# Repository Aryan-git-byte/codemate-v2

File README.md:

# Overview:

# What is this??
Yo, this is a 4x4 custom macropad that you can use for making ur life ezz, lol
it has 16 macros, 2 rotary encoders, RGB lights and an OLED display. and also it is a successor of my previous macropad [Codemate](https://github.com/aryan-git-byte/codemate).
# Use case:
whether you are a programmer, 3d modeller, editor or whatever u can easily use this macropad with just a little bit tweak in its firmware.
# Schematic Overview:
this is the schematic of the project, which u can see here:

you can see the MCU, the key matrix, the LEDs, encoders, everything in this schematic.
# why i made it??
cuz i believe that having a macropad can ezz my workflow and also give make it faster and more efficient.
# PCB overview:
for this i am using a 2 layer pcb board:

# How to Assemble
1. get the pcb ordered and solder all the components to it carefully
2. get these things 3d printed:
    1. [top-plate](3D-models/printable/TopPanel.stl) - 1x
    2. [main-body](3D-models/printable/Main-Body.stl) - 1x
    3. [keycaps](<3D-models/printable/DSA 1u.step>) - 16x
    4. [encoders](3D-models/printable/EncoderKnob.step) - 2x
3. cover it with the top plate
4. drill a 2 mm hole near the red holes:

5. insert 4 m3 inserts in these holes on the main body.
6. Now, put the soldered pcb with all the components inside the main-body
7. put the top panel , and put m3 screws. 
8. now put the keycaps and the knob onto it.
9. enjoy <3
# Firmware:
written in Arduino framework for ESP32-S3 Zero using these libraries:
- [FastLED](https://github.com/FastLED/FastLED) — RGB control
- [Keypad](https://github.com/Chris--A/Keypad) — key matrix
- [Adafruit SSD1306](https://github.com/adafruit/Adafruit_SSD1306) — OLED
- [Adafruit PCF8574](https://github.com/adafruit/Adafruit-PCF8574) — IO expander for encoders
- USB HID (built into ESP32 Arduino core) — keyboard + media keys

### flashing steps:
1. opem [Arduino IDE](https://www.arduino-cc/en/software)
2. add ESP32 board support — paste this in Board Manager URL:
   `https://raw.githubusercontent.com/espressif/arduino-esp32/gh-pages/package_esp32_index.json`
3. install the libraries above from Library Manager
4. select board: `ESP32S3 Dev Module`
5. plug in USB into the devboard
6. upload `firmware/firmware.ino` from this repo
7. done
# BOM:
|item name | quantity | unit price | link | total price
|-|-|-|-|-
Esp32-s3 zero development board|1| 620 rs | [link](https://hubtronics.in/esp32-s3-zero-m?srsltid=AfmBOoq3kT32v8UczG0TNtBfSk1mz6VMTDCRHNpQfM2GaU1SiqyRmEIawpQ)| 620 rs 
Blue MX cherry switches ( pack of 10)| 2 | 350 rs | [link](https://meckeys.com/shop/accessories/keyboard-accessories/key-switches/cherry-mx2a-switch/)| 700 rs
Oled 0.91"|1|198 rs |[link](https://hubtronics.in/0.91inch-4pin-oled-display-module?srsltid=AfmBOookZKpAjyAl9gw9jcReCTK7EAOUjZujy9mtLwreZrFGmea6Y7Tw4Bo)|198 rs 
PCF8574AP | 1 | 124 rs | [link](https://robu.in/product/pcf8574an-texas-instruments-pcf8574an-i-o-expander-8-bit-i2c-2-5-v-6-v-dip-16-pins/)|128 rs
EC11 rotary encoder|2|64 rs | [link](https://www.flyrobo.in/15mm-ec11-rotary-encoder-with-switch-digital-potentiometer?tracking=ads&srsltid=AfmBOoolmlw6qAxzYU2i8ZVPycIOWE9vltP8OnFKiRVbvLtu4q_V_7MlLQc) | 128 rs 
WS2812B | 40 | 4.72 rs | [link](https://hubtronics.in/ws2812b-5050-led?srsltid=AfmBOopNwODVwO3OMV0OqoXZXVZTHtyzRN5Mug-3Q1g00d0sAzbv55LT4r4)| 188.80 rs
470 ohm 0805 resistor (pack of 20)| 1| 8 rs | [link](https://quartzcomponents.com/products/470ohm-470e-5-smd-resistor-0805-pack-of-20-pieces?variant=43515854749930&country=IN&currency=INR&utm_medium=product_sync&utm_source=google&utm_content=sag_organic&utm_campaign=sag_organic&srsltid=AfmBOop0LmdszysC6QKr0nqkLmwG5YoMJAUPzzIZ7T8eKz9CffIsIlRdmUY)|8 rs
100 nF Capacitor 0603 (pack of 20)|2|11 rs | [link](https://quartzcomponents.com/products/kemet-100nf-50v-0603-smd-pack-x7r-multilayer-ceramic-capacitor-10-tolerence-pack-of-20?variant=45972486193386&country=IN&currency=INR&utm_medium=product_sync&utm_source=google&utm_content=sag_organic&utm_campaign=sag_organic&srsltid=AfmBOopnfKv3gKdibyX3qxzEoiDa6hgtUaGOK5H7Lh-MDVl_BFFMZAF-OTY)| 22 rs
 Diode (1N4148)|25|3 rs |[link](https://quartzcomponents.com/products/1n4148-zener-diode?variant=42817413546218&country=IN&currency=INR&utm_medium=product_sync&utm_source=google&utm_content=sag_organic&utm_campaign=sag_organic&srsltid=AfmBOooP8why-3JDRTveRI7fR_9TvlunJk5nlbo3Xbwx15PTjlmVHmHTaeQ)|75 rs
hubtroncs shipping charge| 1 | 75 rs | | 75 rs 
Meckkeys shipping charge | 1 | 100 rs | | 100 rs
FlyRobo shipping | 1 | 59 rs | | 59 rs 

[ Note: the components from the quartz component and robu are budled with my other order of different project, otherwise if u are ordering it for yourself , it will be 100 rs each ]

Total: 2301 rs , (24 usd)

## PCB will be :   

7 usd, shipping will be another 10 usd, but i m getting this shipped along with my different pcb.

# grand total : 31 usd

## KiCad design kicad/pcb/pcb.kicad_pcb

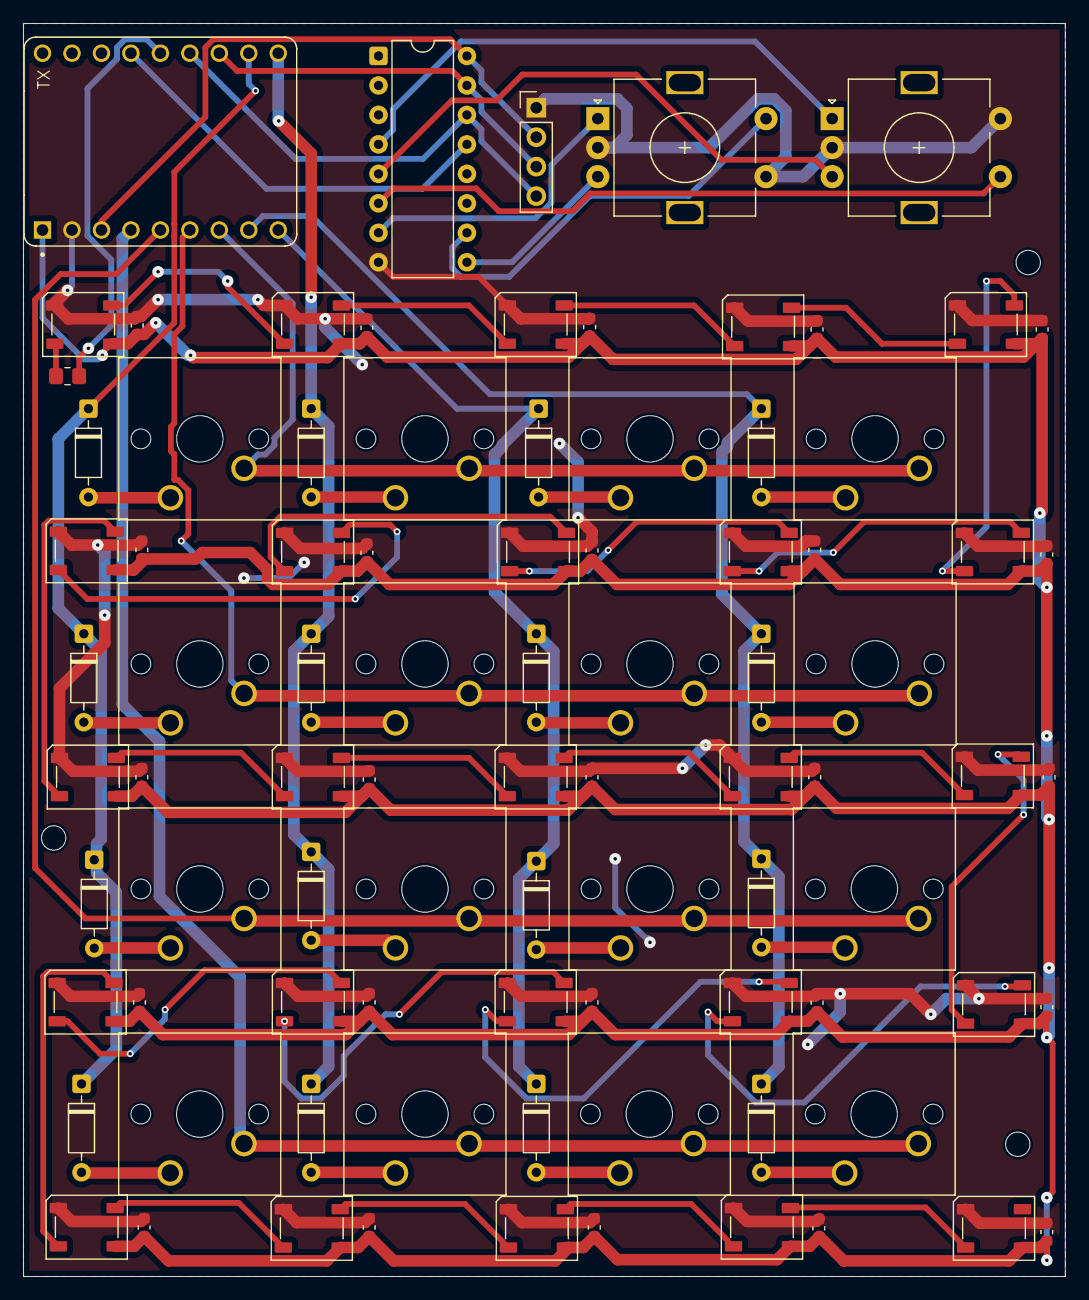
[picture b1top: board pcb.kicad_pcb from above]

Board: 2 copper layers, 89.8 x 108.0 mm, 88 parts (0 on the bottom side), 62 nets.

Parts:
C1, C2, C3, C4, C5, C6, C7, C8, C9, C10, C11, C12, C13, C14, C15, C16, C17, C18, C19, C20, C21, C22, C23, C24, C25: 100 nF; C_0603_1608Metric
D1, D2, D3, D4, D5, D6, D7, D8, D9, D10, D11, D12, D13, D14, D15, D16: D; D_DO-35_SOD27_P7.62mm_Horizontal
D17, D18, D19, D20, D21, D22, D23, D24, D25, D26, D27, D28, D29, D30, D31, D32, D33, D34, D35, D36, D37, D38, D39, D40, D41: WS2812B; LED_WS2812B_PLCC4_5.0x5.0mm_P3.2mm
J1: Conn_01x04; PinHeader_1x04_P2.54mm_Vertical
R1: 470; R_0805_2012Metric_Pad1.20x1.40mm_HandSolder
SW1, SW2, SW3, SW4, SW5, SW6, SW7, SW8, SW9, SW10, SW11, SW12, SW13, SW14, SW15, SW16: SW_SPST; SW_Cherry_MX_1.00u_PCB
SW17, SW18: RotaryEncoder_Switch; RotaryEncoder_Alps_EC11E-Switch_Vertical_H20mm
U1: ESP32-S3-ZERO; MODULE_ESP32-S3-ZERO
U2: PCF8574AP; DIP-16_W7.62mm

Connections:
+3V3: J1.2, U1.3V3 (3V3(OUT)), U2.16 (VDD)
+5V: C1.2, C2.2, C3.2, C4.2, C5.2, C6.2, C7.2, C8.2, C9.2, C10.2, C11.2, C12.2, C13.2, C14.2, C15.2, C16.2, C17.2, C18.2, C19.2, C20.2, C21.2, C22.2, C23.2, C24.2, C25.2, D17.1 (VDD), D18.1 (VDD), D19.1 (VDD), D20.1 (VDD), D21.1 (VDD), D22.1 (VDD), D23.1 (VDD), D24.1 (VDD), D25.1 (VDD), D26.1 (VDD), D27.1 (VDD), D28.1 (VDD), D29.1 (VDD), D30.1 (VDD), D31.1 (VDD), D32.1 (VDD), D33.1 (VDD), D34.1 (VDD), D35.1 (VDD), D36.1 (VDD), D37.1 (VDD), D38.1 (VDD), D39.1 (VDD), D40.1 (VDD), D41.1 (VDD), U1.5V
/INT: U1.12 (GP12), U2.13 (~INT)
/SCL: J1.4, U1.10 (GP10), U2.14 (SCL)
/SDA: J1.3, U1.9 (GP9), U2.15 (SDA)
C1: SW1.2 (B), SW5.2 (B), SW9.2 (B), SW13.2 (B), U1.1 (GP1)
C2: SW2.2 (B), SW6.2 (B), SW10.2 (B), SW14.2 (B), U1.2 (GP2)
C3: SW3.2 (B), SW7.2 (B), SW11.2 (B), SW15.2 (B), U1.3 (GP3)
C4: SW4.2 (B), SW8.2 (B), SW12.2 (B), SW16.2 (B), U1.4 (GP4)
GND: C1.1, C2.1, C3.1, C4.1, C5.1, C6.1, C7.1, C8.1, C9.1, C10.1, C11.1, C12.1, C13.1, C14.1, C15.1, C16.1, C17.1, C18.1, C19.1, C20.1, C21.1, C22.1, C23.1, C24.1, C25.1, D17.3 (VSS), D18.3 (VSS), D19.3 (VSS), D20.3 (VSS), D21.3 (VSS), D22.3 (VSS), D23.3 (VSS), D24.3 (VSS), D25.3 (VSS), D26.3 (VSS), D27.3 (VSS), D28.3 (VSS), D29.3 (VSS), D30.3 (VSS), D31.3 (VSS), D32.3 (VSS), D33.3 (VSS), D34.3 (VSS), D35.3 (VSS), D36.3 (VSS), D37.3 (VSS), D38.3 (VSS), D39.3 (VSS), D40.3 (VSS), D41.3 (VSS), J1.1, SW17.C, SW17.S1, SW18.C, SW18.S2, U1.GND, U2.8 (GND)
unnamed: D1.2 (A), SW1.1 (A)
unnamed: D2.2 (A), SW2.1 (A)
unnamed: D3.2 (A), SW3.1 (A)
unnamed: D4.2 (A), SW4.1 (A)
unnamed: D5.2 (A), SW5.1 (A)
unnamed: D6.2 (A), SW6.1 (A)
unnamed: D7.2 (A), SW7.1 (A)
unnamed: D8.2 (A), SW8.1 (A)
unnamed: D9.2 (A), SW9.1 (A)
unnamed: D10.2 (A), SW10.1 (A)
unnamed: D11.2 (A), SW11.1 (A)
unnamed: D12.2 (A), SW12.1 (A)
unnamed: D13.2 (A), SW13.1 (A)
unnamed: D14.2 (A), SW14.1 (A)
unnamed: D15.2 (A), SW15.1 (A)
unnamed: D16.2 (A), SW16.1 (A)
unnamed: D17.4 (DIN), D18.2 (DOUT)
unnamed: D17.2 (DOUT), D29.4 (DIN)
unnamed: D18.4 (DIN), D19.2 (DOUT)
unnamed: D19.4 (DIN), D28.2 (DOUT)
unnamed: D20.4 (DIN), D21.2 (DOUT)
unnamed: D20.2 (DOUT), D27.4 (DIN)
unnamed: D21.4 (DIN), D22.2 (DOUT)
unnamed: D22.4 (DIN), D30.2 (DOUT)
unnamed: D23.4 (DIN), D24.2 (DOUT)
unnamed: D23.2 (DOUT), D31.4 (DIN)
unnamed: D24.4 (DIN), D25.2 (DOUT)
unnamed: D25.4 (DIN), D26.2 (DOUT)
unnamed: D26.4 (DIN), D27.2 (DOUT)
unnamed: D28.4 (DIN), D36.2 (DOUT)
unnamed: D29.2 (DOUT), D30.4 (DIN)
unnamed: D31.2 (DOUT), D41.4 (DIN)
unnamed: D32.4 (DIN), R1.2
unnamed: D32.2 (DOUT), D33.4 (DIN)
unnamed: D33.2 (DOUT), D34.4 (DIN)
unnamed: D34.2 (DOUT), D35.4 (DIN)
unnamed: D35.2 (DOUT), D36.4 (DIN)
unnamed: D37.4 (DIN), D38.2 (DOUT)
unnamed: D38.4 (DIN), D39.2 (DOUT)
unnamed: D39.4 (DIN), D40.2 (DOUT)
unnamed: D40.4 (DIN), D41.2 (DOUT)
unnamed: R1.1, U1.11 (GP11)
unnamed: SW18.A, U2.4 (P0)
unnamed: SW18.B, U2.5 (P1)
unnamed: SW18.S1, U2.6 (P2)
unnamed: SW17.A, U2.7 (P3)
unnamed: SW17.B, U2.9 (P4)
unnamed: SW17.S2, U2.10 (P5)
R1: D1.1 (K), D2.1 (K), D3.1 (K), D4.1 (K), U1.5 (GP5)
R2: D5.1 (K), D6.1 (K), D7.1 (K), D8.1 (K), U1.6 (GP6)
R3: D9.1 (K), D10.1 (K), D11.1 (K), D12.1 (K), U1.7 (GP7)
R4: D13.1 (K), D14.1 (K), D15.1 (K), D16.1 (K), U1.8 (GP8)

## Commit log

2026-03-26 completed the 3d model
2026-03-26 added stl
2026-05-14 init
2026-05-14 fix gitignore, untrack generated files
2026-05-14 add gerbers, BOM, firmware, schematic, assets, license
2026-05-15 complete
2026-05-15 code
2026-05-15 addon
2026-06-01 added journals
